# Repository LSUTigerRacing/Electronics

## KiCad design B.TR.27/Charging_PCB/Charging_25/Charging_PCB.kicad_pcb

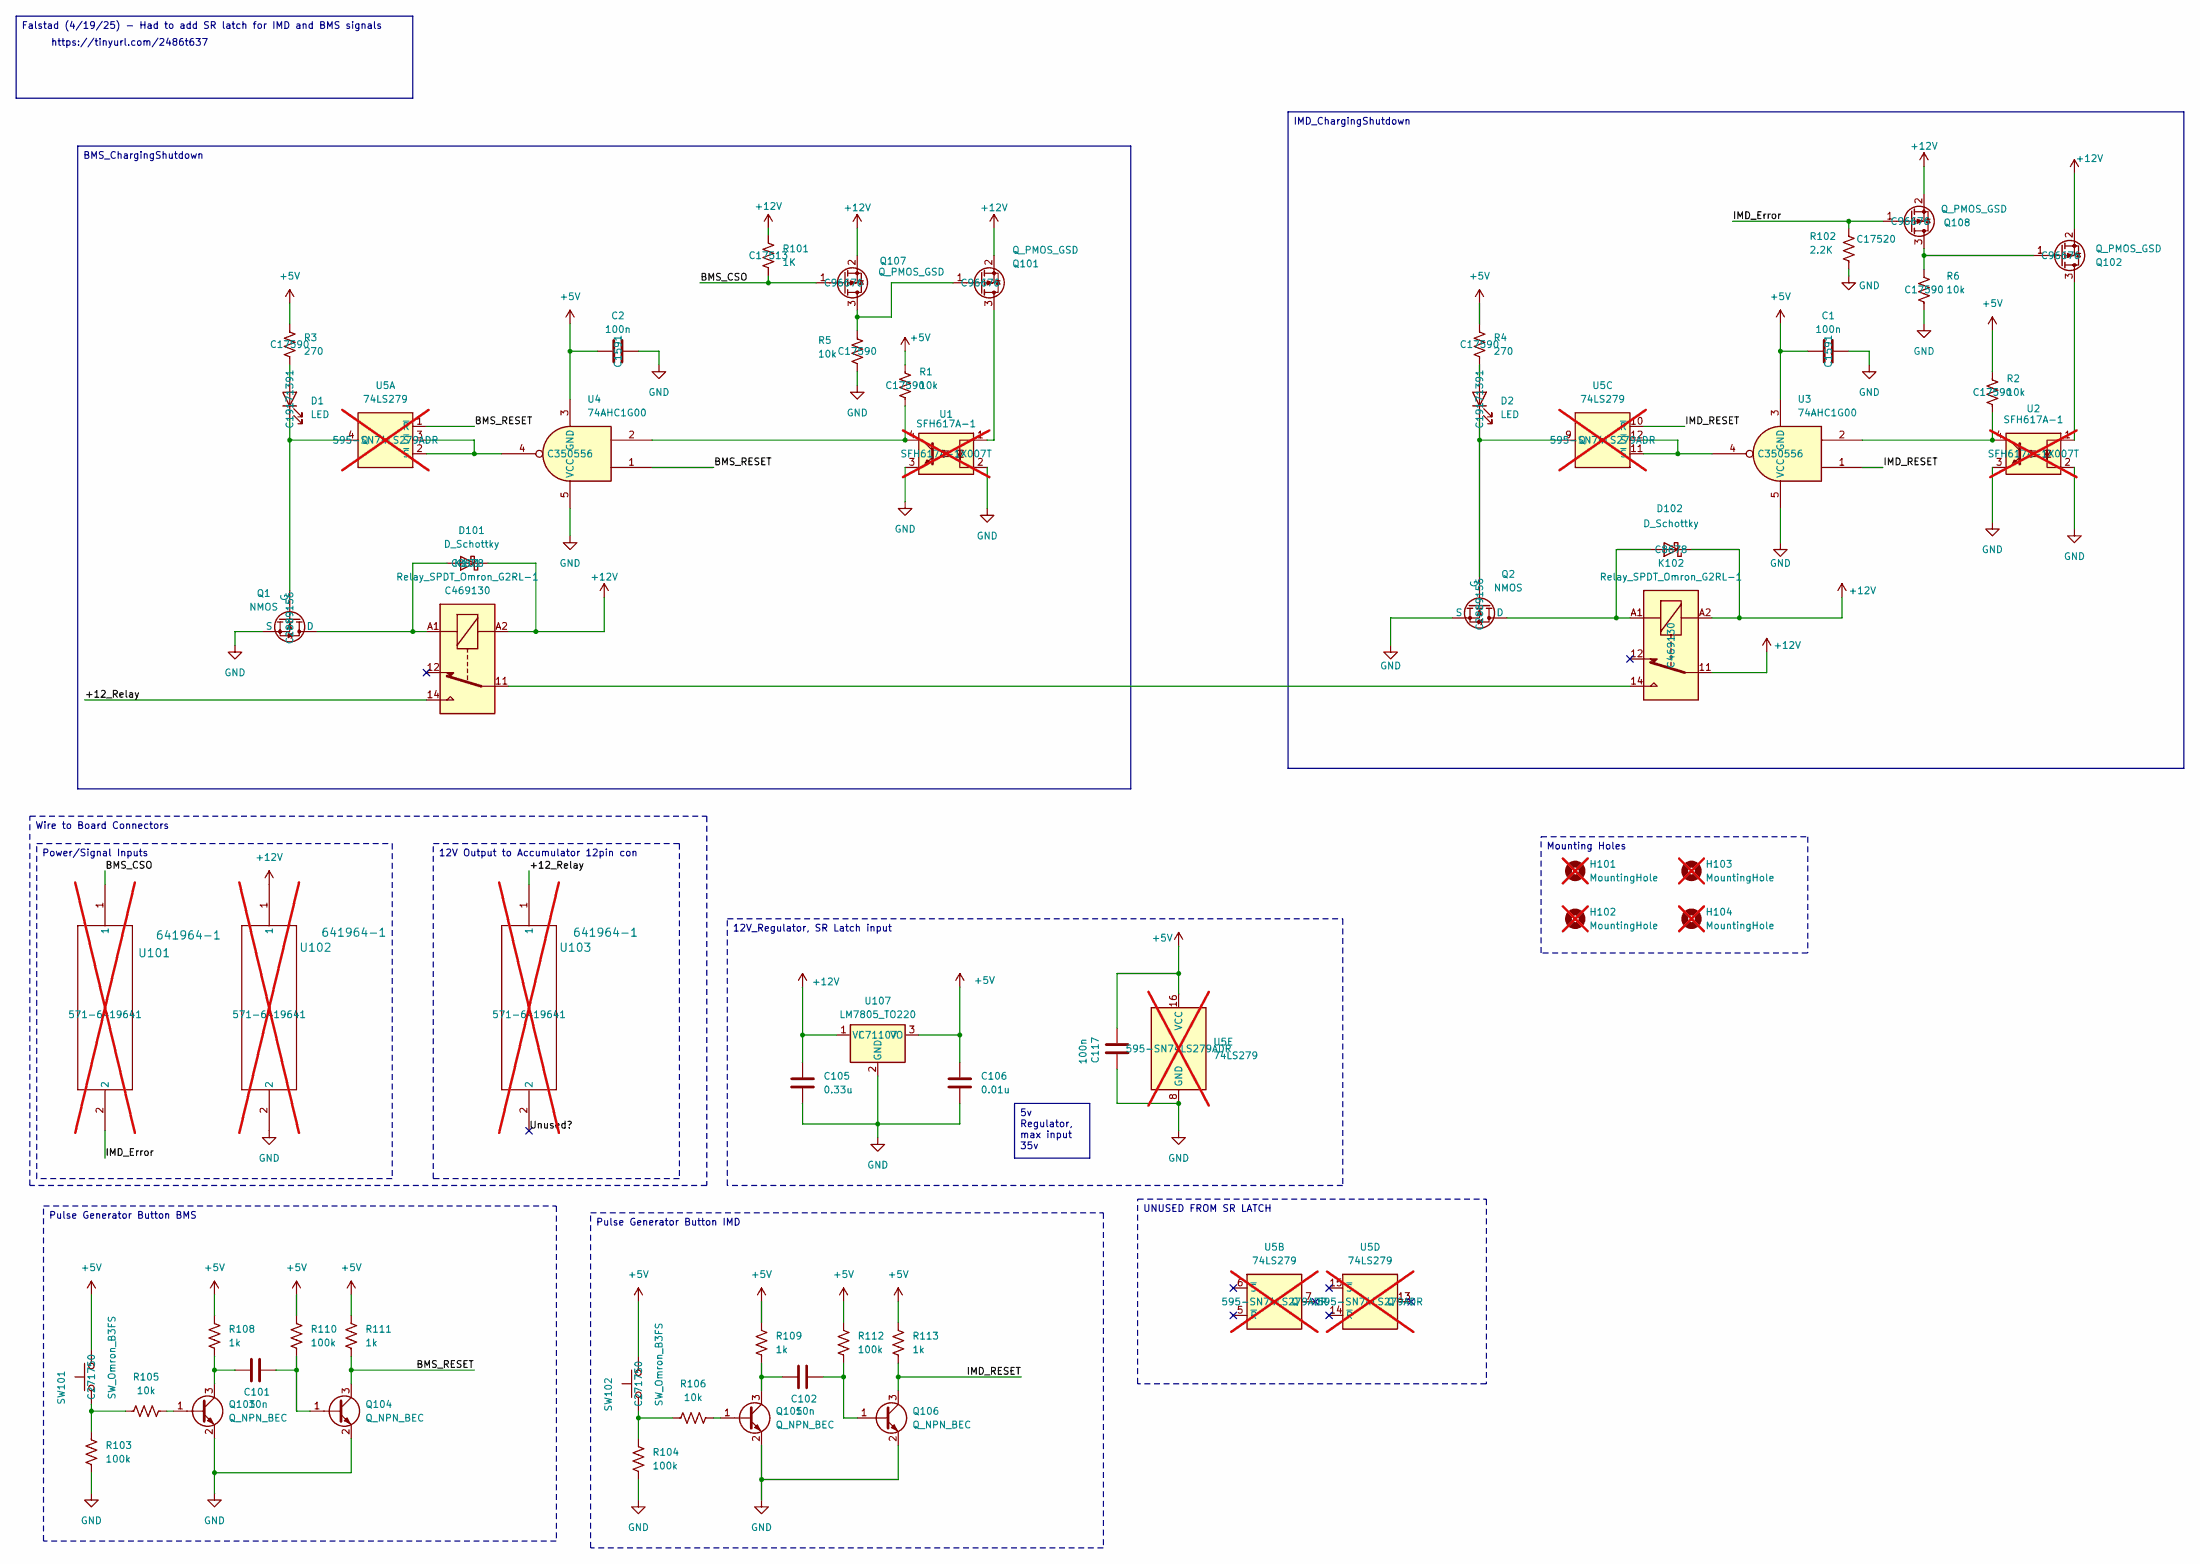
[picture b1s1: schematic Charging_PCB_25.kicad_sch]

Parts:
C1, C2, C117: 100n; C_0603_1608Metric_Pad1.08x0.95mm_HandSolder; JLC# C1591
C101, C102: 10n; C_0603_1608Metric_Pad1.08x0.95mm_HandSolder; JLC# C1589
C105: 0.33u; C_0402_1005Metric; JLC# C107013
C106: 0.01u; C_0402_1005Metric; JLC# C15195
D1, D2: LED; LED_0805_2012Metric_Pad1.15x1.40mm_HandSolder; JLC# C19171391
D101, D102: D_Schottky; D_SMA; JLC# C8678
H101, H102, H103, H104: MountingHole; MountingHole_3.2mm_M3; not fitted
K101, K102: Relay_SPDT_Omron_G2RL-1; JLC# C469130
Q1, Q2: NMOS; TO-252-2; JLC# C2889156
Q101, Q102, Q107, Q108: Q_PMOS_GSD; SOT-523_Custom(C96676); JLC# C96676
Q103, Q104, Q105, Q106: Q_NPN_BEC; SOT-23; JLC# C2146
R1, R2, R5, R6: 10k; R_0805_2012Metric_Pad1.20x1.40mm_HandSolder; JLC# C17590
R3, R4: 270; R_0805_2012Metric_Pad1.20x1.40mm_HandSolder; JLC# C17590
R101: 1K; R_0805_2012Metric_Pad1.20x1.40mm_HandSolder; JLC# C17513
R102: 2.2K; R_0805_2012Metric_Pad1.20x1.40mm_HandSolder; JLC# C17520
R103, R104, R110, R112: 100k; R_0805_2012Metric_Pad1.20x1.40mm_HandSolder; JLC# C149504
R105, R106: 10k; R_0805_2012Metric_Pad1.20x1.40mm_HandSolder; JLC# C17414
R108, R109, R111, R113: 1k; R_0805_2012Metric_Pad1.20x1.40mm_HandSolder; JLC# C17513
SW101, SW102: SW_Omron_B3FS; SW_SPST_Omron_B3FS-100xP; JLC# C271750
U1, U2: SFH617A-1; DIP-4_W7.62mm; MOUSER SFH617A-1X007T; not fitted
U3, U4: 74AHC1G00; SOT-23-5; JLC# C350556
U5: 74LS279; SOIC-16_3.9x9.9mm_P1.27mm; MOUSER 595-SN74LS279ADR; not fitted
U101, U102, U103: 641964-1; TE_641964-1; MOUSER 571-6419641; not fitted
U107: LM7805_TO220; TO-220-3_Vertical; JLC# C71107

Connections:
+5V: C1.1, C2.1, C106.1, C117.1, R1.1, R2.1, R3.1, R4.1, R108.1, R109.1, R110.1, R111.1, R112.1, R113.1, SW101.2, SW102.2, U3.3 (GND), U4.3 (GND), U5.16 (VCC), U107.3 (VO)
+12V: C105.1, D101.1 (K), D102.1 (K), K101.A2, K102.11, K102.A2, Q101.2 (S), Q102.2 (S), Q107.2 (S), Q108.2 (S), R101.1, U102.1, U107.1 (VI)
/+12_Relay: K101.14, U103.1
/BMS_CSO: Q107.1 (G), R101.2, U101.1
/BMS_RESET: Q104.3 (C), R111.2, U4.1, U5.1 (~R)
/IMD_Error: Q108.1 (G), R102.1, U101.2
/IMD_RESET: Q106.3 (C), R113.2, U3.1, U5.10 (~R)
/Unused?: U103.2
GND: C1.2, C2.2, C105.2, C106.2, C117.2, Q1.3 (S), Q2.3 (S), Q103.2 (E), Q104.2 (E), Q105.2 (E), Q106.2 (E), R5.2, R6.2, R102.2, R103.2, R104.2, U1.2, U1.3, U2.2, U2.3, U3.5 (VCC), U4.5 (VCC), U5.8 (GND), U102.2, U107.2 (GND)
unnamed: D1.2 (A), R3.2
unnamed: D1.1 (K), Q1.2 (G), U5.4 (Q)
unnamed: D2.2 (A), R4.2
unnamed: D2.1 (K), Q2.2 (G), U5.9 (Q)
unnamed: D101.2 (A), K101.A1, Q1.1 (D)
unnamed: D102.2 (A), K102.A1, Q2.1 (D)
unnamed: K101.11, K102.14
unnamed: Q101.3 (D), U1.1
unnamed: Q101.1 (G), Q107.3 (D), R5.1
unnamed: Q102.3 (D), U2.1
unnamed: Q102.1 (G), Q108.3 (D), R6.1
unnamed: Q103.1 (B), R105.1
unnamed: C101.1, Q103.3 (C), R108.2
unnamed: C101.2, Q104.1 (B), R110.2
unnamed: Q105.1 (B), R106.1
unnamed: C102.1, Q105.3 (C), R109.2
unnamed: C102.2, Q106.1 (B), R112.2
unnamed: R1.2, U1.4, U4.2
unnamed: R2.2, U2.4, U3.2
unnamed: R103.1, R105.2, SW101.1
unnamed: R104.1, R106.2, SW102.1
unnamed: U3.4, U5.11 (~S), U5.12 (~S)
unnamed: U4.4, U5.2 (~S), U5.3 (~S)

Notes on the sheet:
https://tinyurl.com/2486t637
12V_Regulator, SR Latch input
12V Output to Accumulator 12pin con
Power/Signal Inputs
Wire to Board Connectors
IMD_ChargingShutdown
Pulse Generator Button BMS
Falstad (4/19/25) - Had to add SR latch for IMD and BMS signals
Pulse Generator Button IMD
UNUSED FROM SR LATCH
Mounting Holes
BMS_ChargingShutdown
5v Regulator, max input 35v

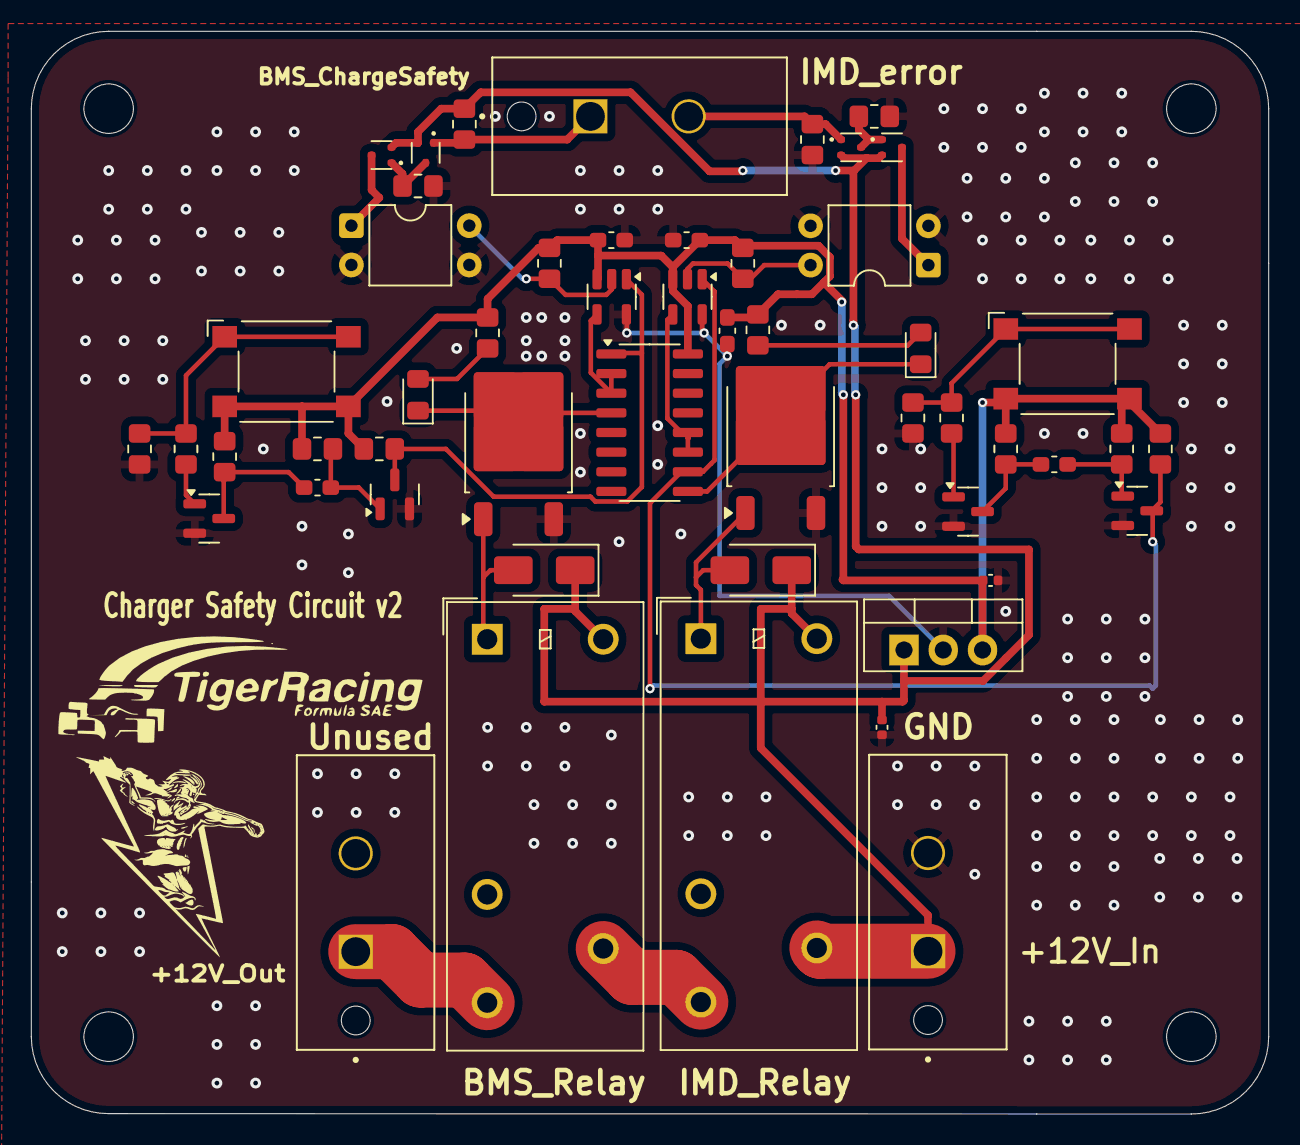
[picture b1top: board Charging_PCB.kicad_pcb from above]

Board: 2 copper layers, 80.0 x 70.0 mm, 56 parts (0 on the bottom side), 31 nets.

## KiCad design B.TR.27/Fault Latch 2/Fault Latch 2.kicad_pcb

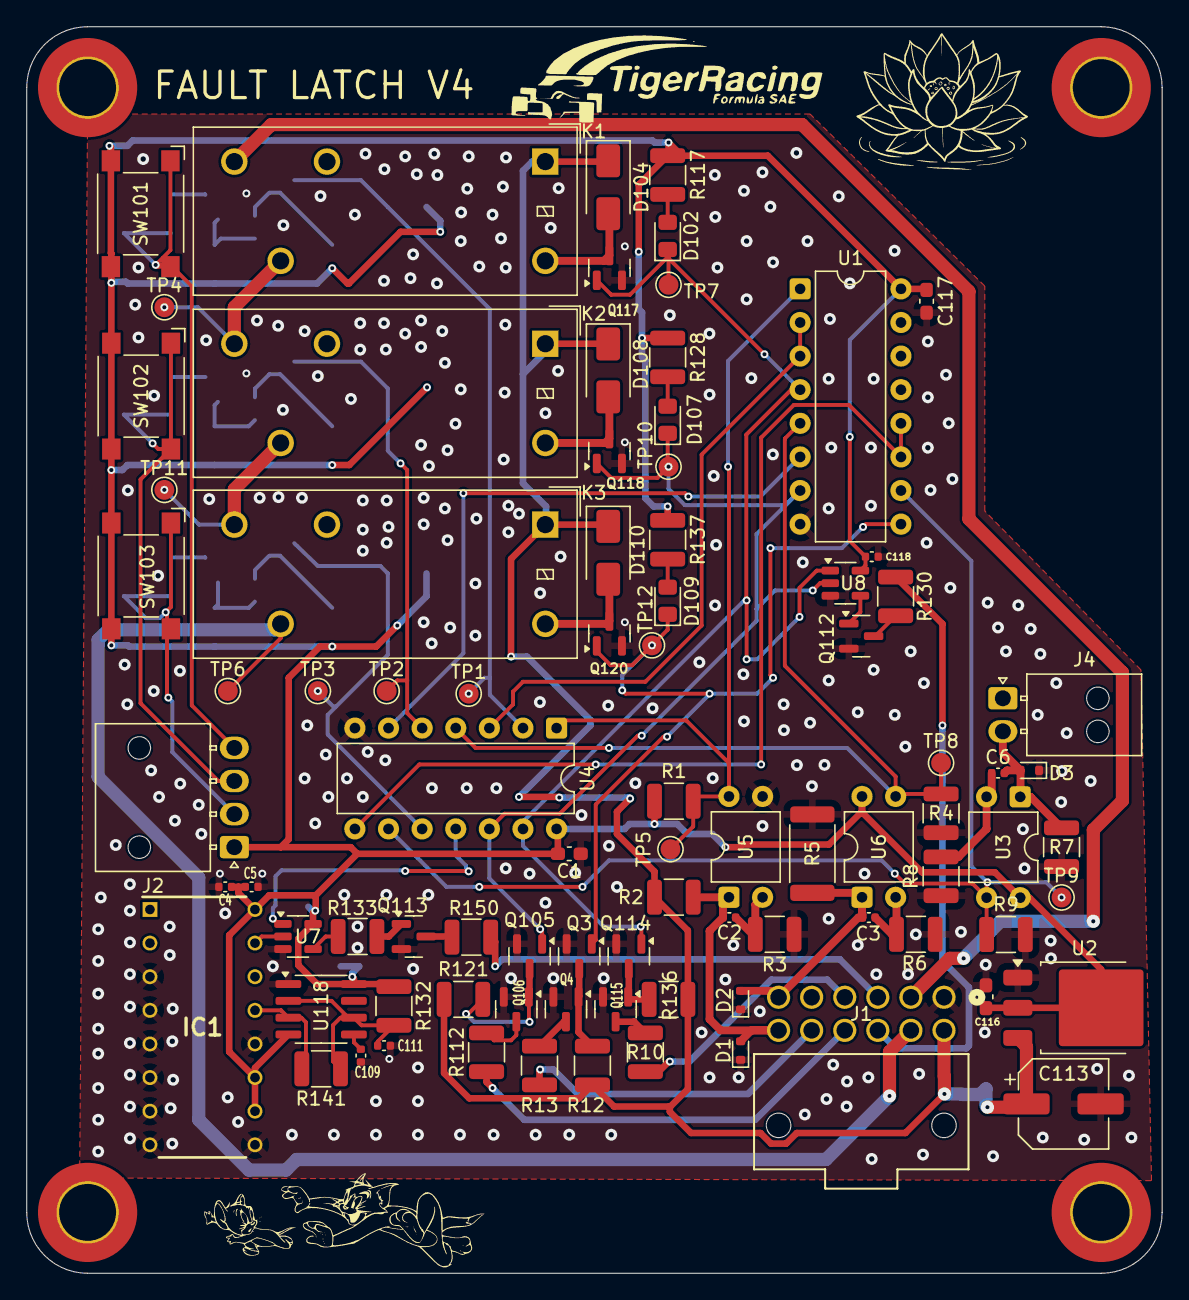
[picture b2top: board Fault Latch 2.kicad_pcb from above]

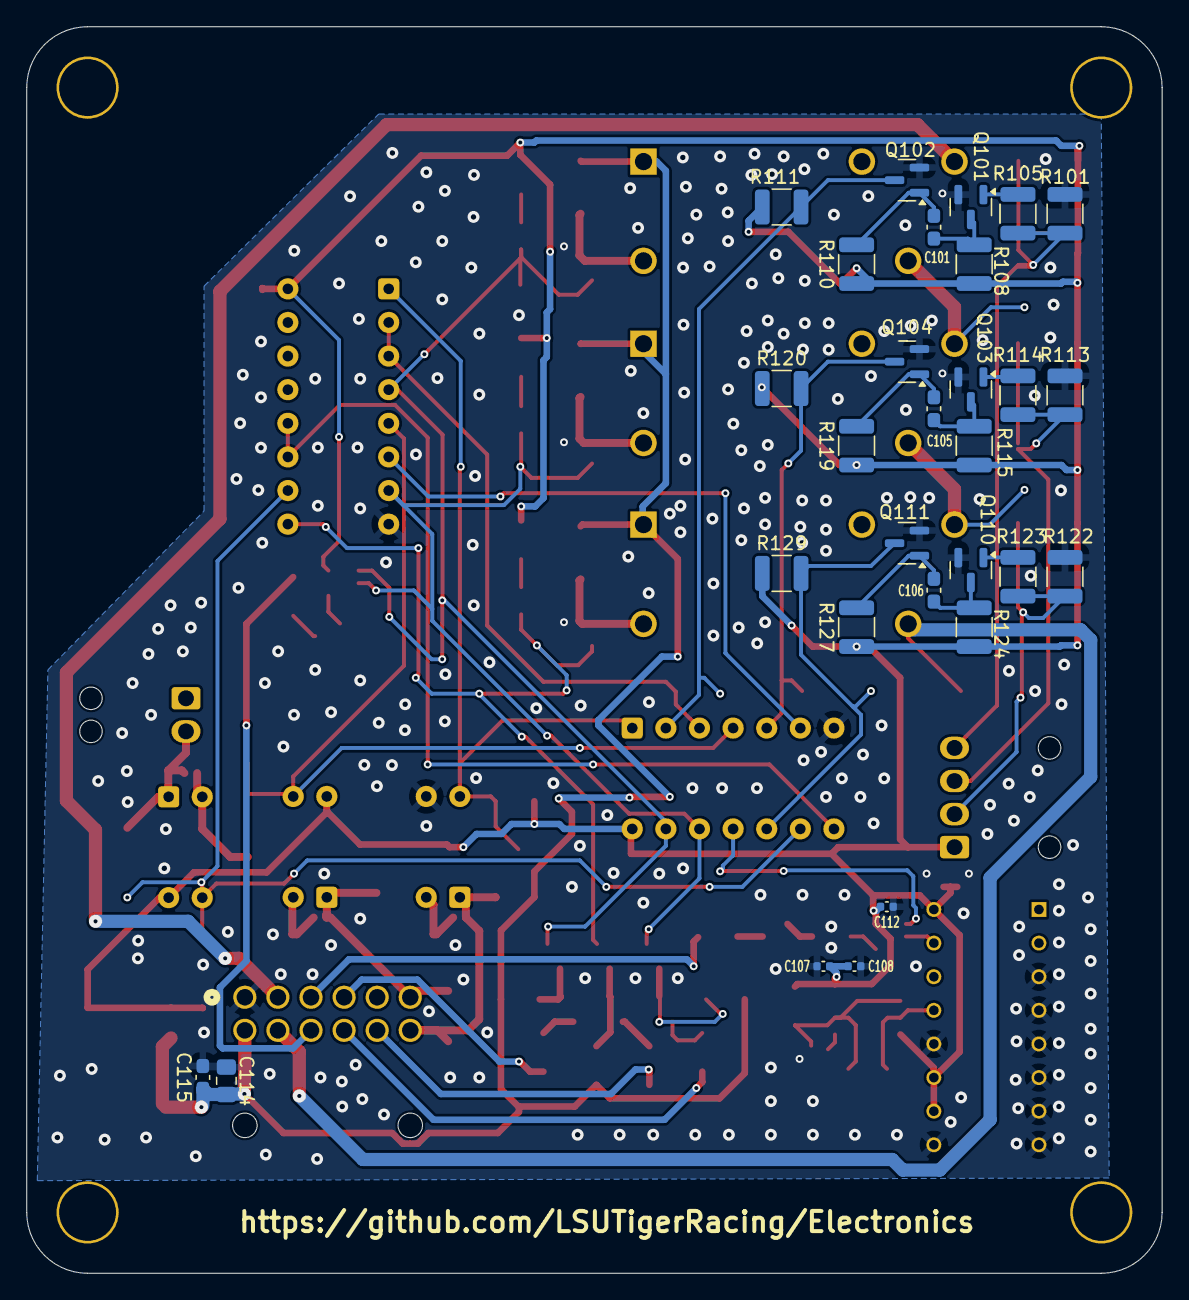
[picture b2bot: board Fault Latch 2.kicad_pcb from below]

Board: 2 copper layers, 85.8 x 94.2 mm, 119 parts (29 on the bottom side), 64 nets.

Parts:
C1, C116, C117: 100n; C_0603_1608Metric_Pad1.08x0.95mm_HandSolder
C2, C3, C5, C6, C108, C112, C118: 0.1u; C_0402_1005Metric
C4, C107: 1u; C_0402_1005Metric
C101, C105, C106: 10n; C_0603_1608Metric_Pad1.08x0.95mm_HandSolder
C109: .01u; C_0402_1005Metric
C111: 22u; C_0402_1005Metric
C113: 47u; CP_Elec_6.3x5.4
C114: 1u; C_0805_2012Metric_Pad1.18x1.45mm_HandSolder
C115: 0.33u; C_0603_1608Metric_Pad1.08x0.95mm_HandSolder
D1, D2, D3: Bi-TVS Diode; D_SOD-523
D102, D107, D109: RED; LED_0805_2012Metric_Pad1.15x1.40mm_HandSolder
D104, D108, D110: D_Schottky; D_SMA
H101, H102, H103, H104: MountingHole; MountingHole_4.3mm_M4_DIN965_Pad_TopOnly
IC1: CD4027BE; DIP794W53P254L1930H508Q16N
J1: 1053141312; CONN_SD-105314-100_12_MOL_Nano
J2: 4pinNanofit; Molex_Nano-Fit_105313-xx04_1x04_P2.50mm_Horizontal
J4: 1053131202; Molex_Nano-Fit_105313-xx02_1x02_P2.50mm_Horizontal
K1, K2, K3: Relay_SPDT_Omron_G2RL-1
Q3, Q4, Q105, Q106, Q112, Q113, Q114, Q115, Q117, Q118, Q120: Q_NMOS_GSD; SOT-23
Q101, Q102, Q103, Q104, Q110, Q111: Q_NPN_BEC; SOT-23
R1, R4, R7, R9, R12, R105, R114, R121, R123, R136: 10k; R_1210_3225Metric
R2, R6, R8, R108, R111, R115, R120, R124, R129: 1k; R_1210_3225Metric
R3, R130, R150: 270R; R_1210_3225Metric
R5: 2.2k; R_2512_6332Metric
R10, R13, R112: 510R; R_1210_3225Metric
R101, R110, R113, R119, R122, R127, R132: 100k; R_1210_3225Metric
R117, R128, R137: 2k; R_1210_3225Metric
R133: 680; R_1210_3225Metric
R141: 5.6k; R_1210_3225Metric
SW101, SW102, SW103: SW_Omron_B3FS; SW_SPST_Omron_B3FS-100xP
TP1, TP2, TP3, TP4, TP5, TP6, TP7, TP8, TP9, TP10, TP11, TP12: TestPoint; TestPoint_Pad_D1.5mm
U1: 74LS279; DIP-16_W7.62mm
U2: LM1117DT-5.0; TO-252-3_TabPin2
U3, U5, U6: SFH617A-1; DIP-4_W7.62mm
U4: 74HC00; DIP-14_W7.62mm
U7, U8: SN74AHC1G08DBVR; SOT-23-5
U118: LM555xM; SOIC-8_3.9x4.9mm_P1.27mm

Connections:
+5V: C1.1, C4.1, C5.1, C107.1, C108.1, C112.2, C116.2, C117.1, C118.2, IC1.10 (J1), IC1.11 (K1), IC1.16 (VDD), J2.1, R1.1, R108.1, R110.1, R111.1, R115.1, R117.2, R119.1, R120.1, R124.1, R127.1, R128.2, R129.1, R132.2, R137.2, SW101.2, SW102.2, SW103.2, U1.16 (VCC), U2.2 (VO), U3.4, U4.14 (VCC), U6.4, U7.5 (VCC), U8.5 (VCC), U118.4 (R), U118.8 (VCC)
+12V: C113.1, C114.1, C115.1, D104.1 (K), D108.1 (K), D110.1 (K), J1.7, K1.A1, K2.A1, K3.A1, R2.1, R12.1, R121.1, R136.1, U2.3 (VI)
/BMS: C2.1, D1.2 (A2), J1.12, R2.2, U5.1
/BMS Button -: J2.4, R101.1, R105.2, SW101.1
/BMS Light -: J1.4, R10.1
/BMS_SR: D102.1 (K), Q114.1 (G), Q117.1 (G), TP7.1, U1.4 (Q), U4.13, U8.1
/BSPD: C6.1, D3.2 (A2), J4.2, R7.1, U3.1
/BSPD Button -: J2.2, R122.1, R123.2, SW103.1
/BSPD Light -: J1.11, R13.1
/BSPD_SR: D109.1 (K), Q3.1 (G), Q120.1 (G), TP12.1, U1.9 (Q)
/CLOCK: IC1.15 (Q1), U7.2
/IMD: C3.1, D2.2 (A2), J1.6, R5.1, U6.1
/IMD Button -: J2.3, R113.1, R114.2, SW102.1
/IMD Light -: J1.10, R112.1
/IMD_SR: D107.1 (K), Q105.1 (G), Q118.1 (G), TP10.1, U1.7 (Q), U4.12, U8.2
/NBMS_LV: R1.2, TP5.1, U1.1 (~R), U4.1, U5.4
/NBPSD_LV: R9.1, TP9.1, U1.10 (~R), U3.3, U4.9
/NIMD_LV: R4.1, TP8.1, U1.5 (~R), U4.4, U6.3
/NRESET_BMS: Q102.3 (C), R111.2, TP1.1, U4.2
/NRESET_BSPD: Q111.3 (C), R129.2, TP3.1, U4.10
/NRESET_IMD: Q104.3 (C), R120.2, TP2.1, U4.5
/Shutdown Circuit In: J1.2, K1.14
/Shutdown Circuit Out: J1.8, K3.11, TP6.1
/THRESH: C111.2, R132.1, R141.2, U118.2 (TR), U118.6 (THR)
/TSSI Green -: J1.9, R130.2
/TSSI Red -: J1.3, R150.2
GND: C1.2, C4.2, C5.2, C107.2, C108.2, C109.2, C111.1, C112.1, C113.2, C114.2, C115.2, C116.1, C117.2, C118.1, D1.1 (A1), D2.1 (A1), D3.1 (A1), IC1.3 (CLOCK2), IC1.4 (RESET2), IC1.5 (K2), IC1.6 (J2), IC1.7 (SET2), IC1.8 (VSS), IC1.9 (SET1), IC1.12 (RESET1), J1.1, Q3.2 (S), Q4.2 (S), Q101.2 (E), Q102.2 (E), Q103.2 (E), Q104.2 (E), Q105.2 (S), Q106.2 (S), Q110.2 (E), Q111.2 (E), Q112.2 (S), Q113.2 (S), Q114.2 (S), Q115.2 (S), Q117.2 (S), Q118.2 (S), Q120.2 (S), R3.1, R4.2, R5.2, R6.2, R7.2, R8.2, R9.2, R101.2, R113.2, R122.2, U1.8 (GND), U2.1 (GND), U4.7 (GND), U5.3, U7.3 (GND), U8.3 (GND), U118.1 (GND)
unnamed: C2.2, R3.2, U5.2
unnamed: C3.2, R6.1, U6.2
unnamed: C6.2, R8.1, U3.2
unnamed: D102.2 (A), R117.1
unnamed: D104.2 (A), K1.A2, Q117.3 (D)
unnamed: D107.2 (A), R128.1
unnamed: D108.2 (A), K2.A2, Q118.3 (D)
unnamed: D109.2 (A), R137.1
unnamed: D110.2 (A), K3.A2, Q120.3 (D)
unnamed: IC1.13 (CLOCK1), R141.1, U118.3 (Q)
unnamed: K1.11, K2.14, TP4.1
unnamed: K2.11, K3.14, TP11.1
unnamed: Q3.3 (D), Q4.1 (G), R12.2
unnamed: Q4.3 (D), R13.2
unnamed: Q101.1 (B), R105.1
unnamed: C101.1, Q101.3 (C), R108.2
unnamed: C101.2, Q102.1 (B), R110.2
unnamed: Q103.1 (B), R114.1
unnamed: C105.1, Q103.3 (C), R115.2
unnamed: C105.2, Q104.1 (B), R119.2
unnamed: Q105.3 (D), Q106.1 (G), R121.2
unnamed: Q106.3 (D), R112.2
unnamed: Q110.1 (B), R123.1
unnamed: C106.1, Q110.3 (C), R124.2
unnamed: C106.2, Q111.1 (B), R127.2
unnamed: Q112.3 (D), R130.1
unnamed: Q112.1 (G), U8.4
unnamed: Q113.3 (D), R150.1
unnamed: Q113.1 (G), R133.1
unnamed: Q114.3 (D), Q115.1 (G), R136.2
unnamed: Q115.3 (D), R10.2
unnamed: R133.2, U7.4
unnamed: U1.2 (~S), U1.3 (~S), U4.3
unnamed: U1.6 (~S), U4.6
unnamed: U1.11 (~S), U1.12 (~S), U4.8
unnamed: U4.11, U7.1
unnamed: C109.1, U118.5 (CV)

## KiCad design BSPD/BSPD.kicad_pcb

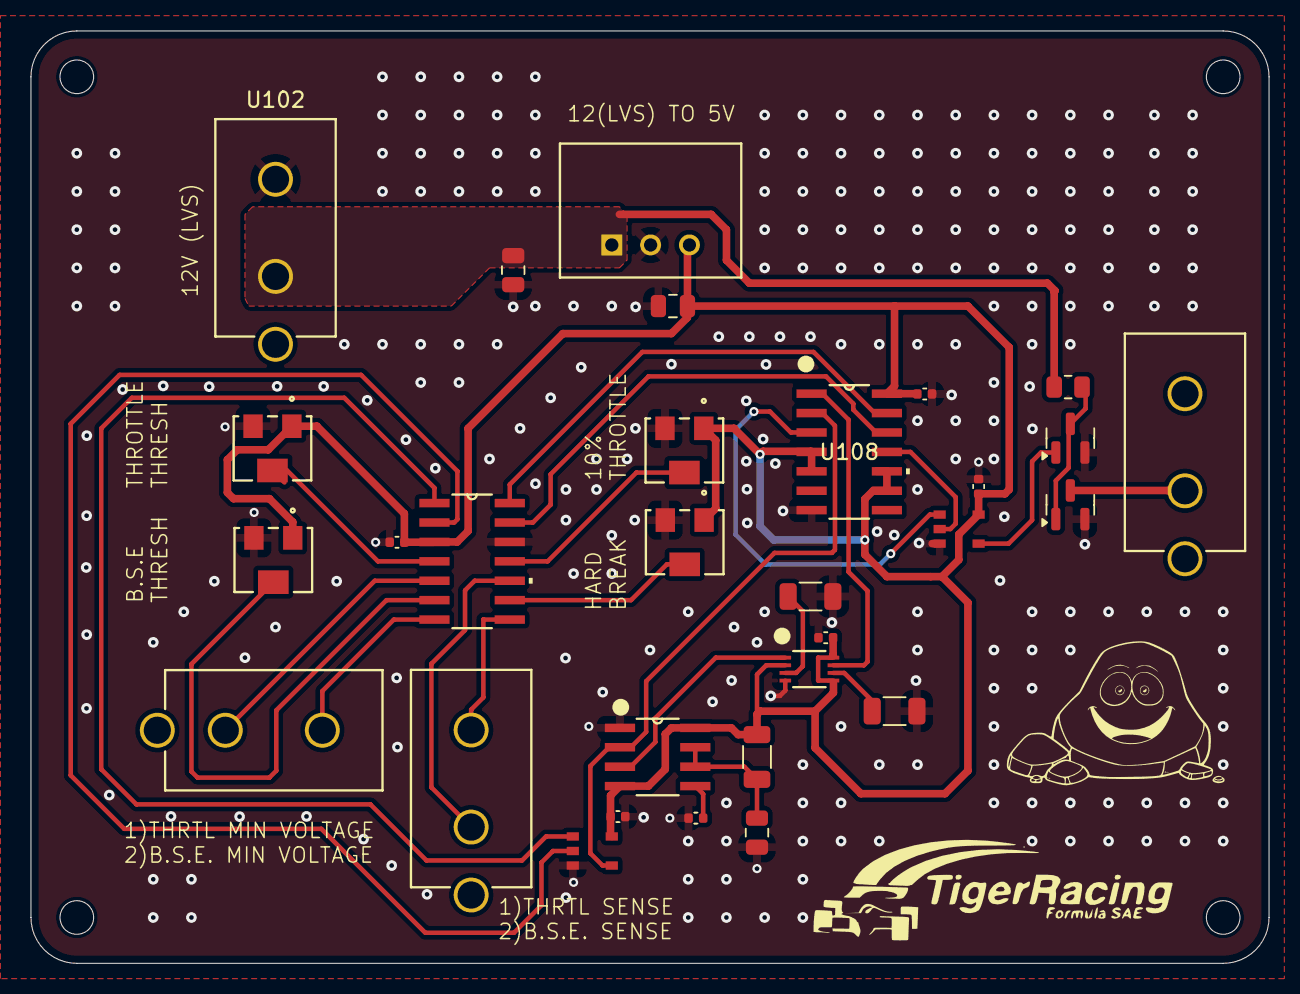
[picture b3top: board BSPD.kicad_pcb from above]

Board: 2 copper layers, 81.0 x 61.0 mm, 34 parts (0 on the bottom side), 27 nets.

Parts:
C101, C103, C106, C107, C109: 0.1uF; C_0402_1005Metric
C102, C104, C108: 10uF; C_0805_2012Metric
C105: 0.01uF; C_0402_1005Metric
H101, H102, H103, H104: MountingHole; MountingHole_2.2mm_M2
Q1, Q2: Q_NMOS_GSD; SOT-23
R1: 10k; R_0805_2012Metric
R101, R102, R103: 10K; R_1206_3216Metric
RV101, RV102, RV103, RV104: 10K; POT_3224W
U101, U102, U110, U111: 641964-1; 641964-1_TYC
U103: R-78E5.0-0.5; R-78E-0.5_RCP
U104, U109: SN74LVC1G08DBVR; DBV0005A_L
U105: LM339DR; D14
U106: NE555DR; D8
U107: SN74LVC3G14DCUR; DCU8_TEX
U108: SN74AC32DR; D14

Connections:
1OUT: U104.1 (A), U105.1 (1OUT)
2OUT: U104.2 (B), U105.2 (2OUT)
3OUT: U105.14 (OUT3), U108.13 (4B)
4OUT: U105.13 (OUT4), U108.12 (4A)
10%_THROTTLE: RV103.2, U105.11 (4IN+)
+5V: C101.1, C103.1, C104.1, C106.1, C107.1, C109.1, R103.1, RV101.1, RV102.1, RV103.1, RV104.1, U103.3 (+VOUT), U104.5 (V+), U105.3 (VCC), U106.4 (RESET), U106.8 (VCC), U107.2 (3Y), U107.5 (2Y), U107.8 (VCC), U108.4 (2A), U108.5 (2B), U108.9 (3A), U108.10 (3B), U108.14 (VCC), U109.5 (V+)
+12V: C102.1, R1.1, U102.1, U103.1 (+VIN)
BSE_IN: U101.2, U105.7 (1IN+)
BSE_Sense_IN: U105.8 (3IN-), U111.2
BSPD_TO_FAULT: Q2.3 (D), U110.1
GND: C101.2, C102.2, C103.2, C104.2, C105.2, C106.2, C107.2, C108.2, C109.2, Q1.2 (S), Q2.2 (S), R101.2, R102.2, RV101.3, RV102.3, RV103.3, RV104.3, U102.2, U103.2 (GND), U104.3 (V-), U105.12 (GND), U106.1 (GND), U107.4 (GND), U108.7 (GND), U109.3 (V-)
HARD_BREAK: RV104.2, U105.9 (3IN+)
unnamed: Q1.3 (D), Q2.1 (G), R1.2
unnamed: Q1.1 (G), U109.4 (Y)
unnamed: U104.4 (Y), U106.2 (TRIG), U108.2 (1B)
unnamed: C105.1, U106.5 (CONT)
unnamed: C108.1, R103.2, U106.6 (THRES), U106.7 (DISCH)
unnamed: U106.3 (OUT), U107.1 (1A)
unnamed: U107.7 (1Y), U108.1 (1A)
unnamed: R101.1, U107.3 (2A)
unnamed: R102.1, U107.6 (3A)
unnamed: U108.3 (1Y), U109.1 (A)
unnamed: U108.11 (4Y), U109.2 (B)
THRESH_BSE: RV101.2, U105.6 (1IN-)
THRESH_THROTTLE: RV102.2, U105.4 (2IN-)
THROTTLE_IN: U101.1, U105.5 (2IN+)
THROTTLE_Sense_IN: U105.10 (4IN-), U111.1

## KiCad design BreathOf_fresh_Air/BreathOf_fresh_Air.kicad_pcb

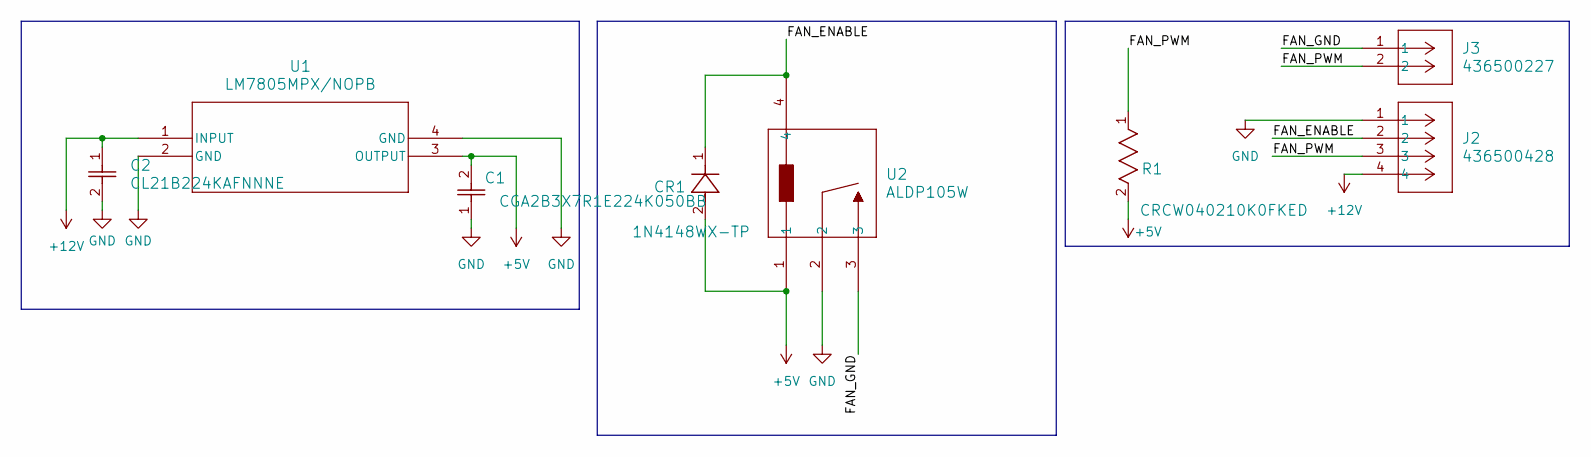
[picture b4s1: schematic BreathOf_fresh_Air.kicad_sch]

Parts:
C1: CGA2B3X7R1E224K050BB; CAP_1005_TDK
C2: CL21B224KAFNNNE; CAP_CL21_SAM
CR1: 1N4148WX-TP; CR_SOD323_MCC
J2: 436500428; CONN_SD-43650-010_04_MOL
J3: 436500227; CONN_SD-43650-010_02_MOL
R1: CRCW040210K0FKED; RES_CRCW_0402
U1: LM7805MPX/NOPB; DCY4_TEX
U2: ALDP105W; PAN_ALD_PAN

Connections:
+5V: C1.2, CR1.2, R1.2, U1.3 (OUTPUT), U2.1
+12V: C2.1, J2.4, U1.1 (INPUT)
/FAN_ENABLE: CR1.1, J2.2, U2.4
/FAN_GND: J3.1, U2.3
/FAN_PWM: J2.3, J3.2, R1.1
GND: C1.1, C2.2, J2.1, U1.2 (GND), U1.4 (GND), U2.2

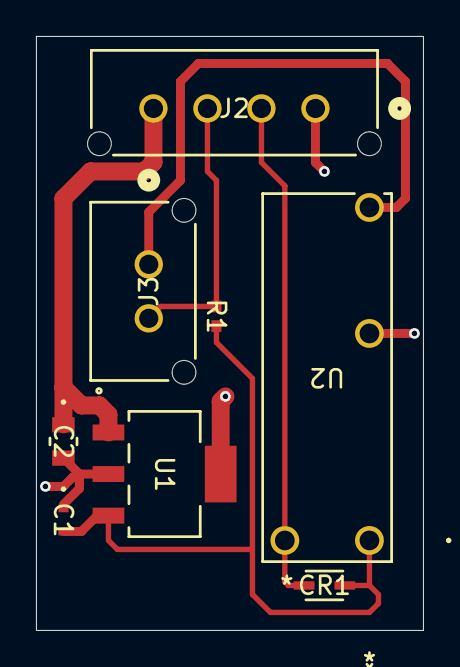
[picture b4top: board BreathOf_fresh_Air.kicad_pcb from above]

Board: 2 copper layers, 21.5 x 33.0 mm, 8 parts (0 on the bottom side), 6 nets.

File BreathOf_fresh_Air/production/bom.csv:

Designator,Footprint,Quantity,Value,LCSC Part #
C1,CAP_1005_TDK,1,CGA2B3X7R1E224K050BB,
C2,CAP_CL21_SAM,1,CL21B224KAFNNNE,
CR1,CR_SOD323_MCC,1,1N4148WX-TP,
J2,CONN_SD-43650-010_04_MOL,1,436500428,
J3,CONN_SD-43650-010_02_MOL,1,436500227,
R1,RES_CRCW_0402,1,CRCW040210K0FKED,
U1,DCY4_TEX,1,LM7805MPX/NOPB,
U2,PAN_ALD_PAN,1,ALDP105W,
